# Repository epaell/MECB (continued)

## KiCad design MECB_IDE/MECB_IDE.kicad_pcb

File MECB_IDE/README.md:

# MECB IDE Board
An implementation of a parallel IDE board for the MECB system. The hardware is based on the PPIDE available for the RC2014 system (https://rc2014.co.uk/modules/ide-hard-drive-module/) and should be compatible with that and with RomWBW. The PLD is set to select the PPIDE device at ports $20-$23 (or $XX20-$XX23 on the MECB memory map if used with CPUs without a separate I/O map) - this is also the default port setting used by RomWBW. Here is the completed board with a compact FLASH to IDE adapter attached to the board:

I have confirmed that v1.0 of the board works using the 44-pin IDE connector. Note that Pin 20 of the 40 pin IDE header and the 44 pin IDE header should be removed as they act as a guide for devices/cables that plug directly into it:

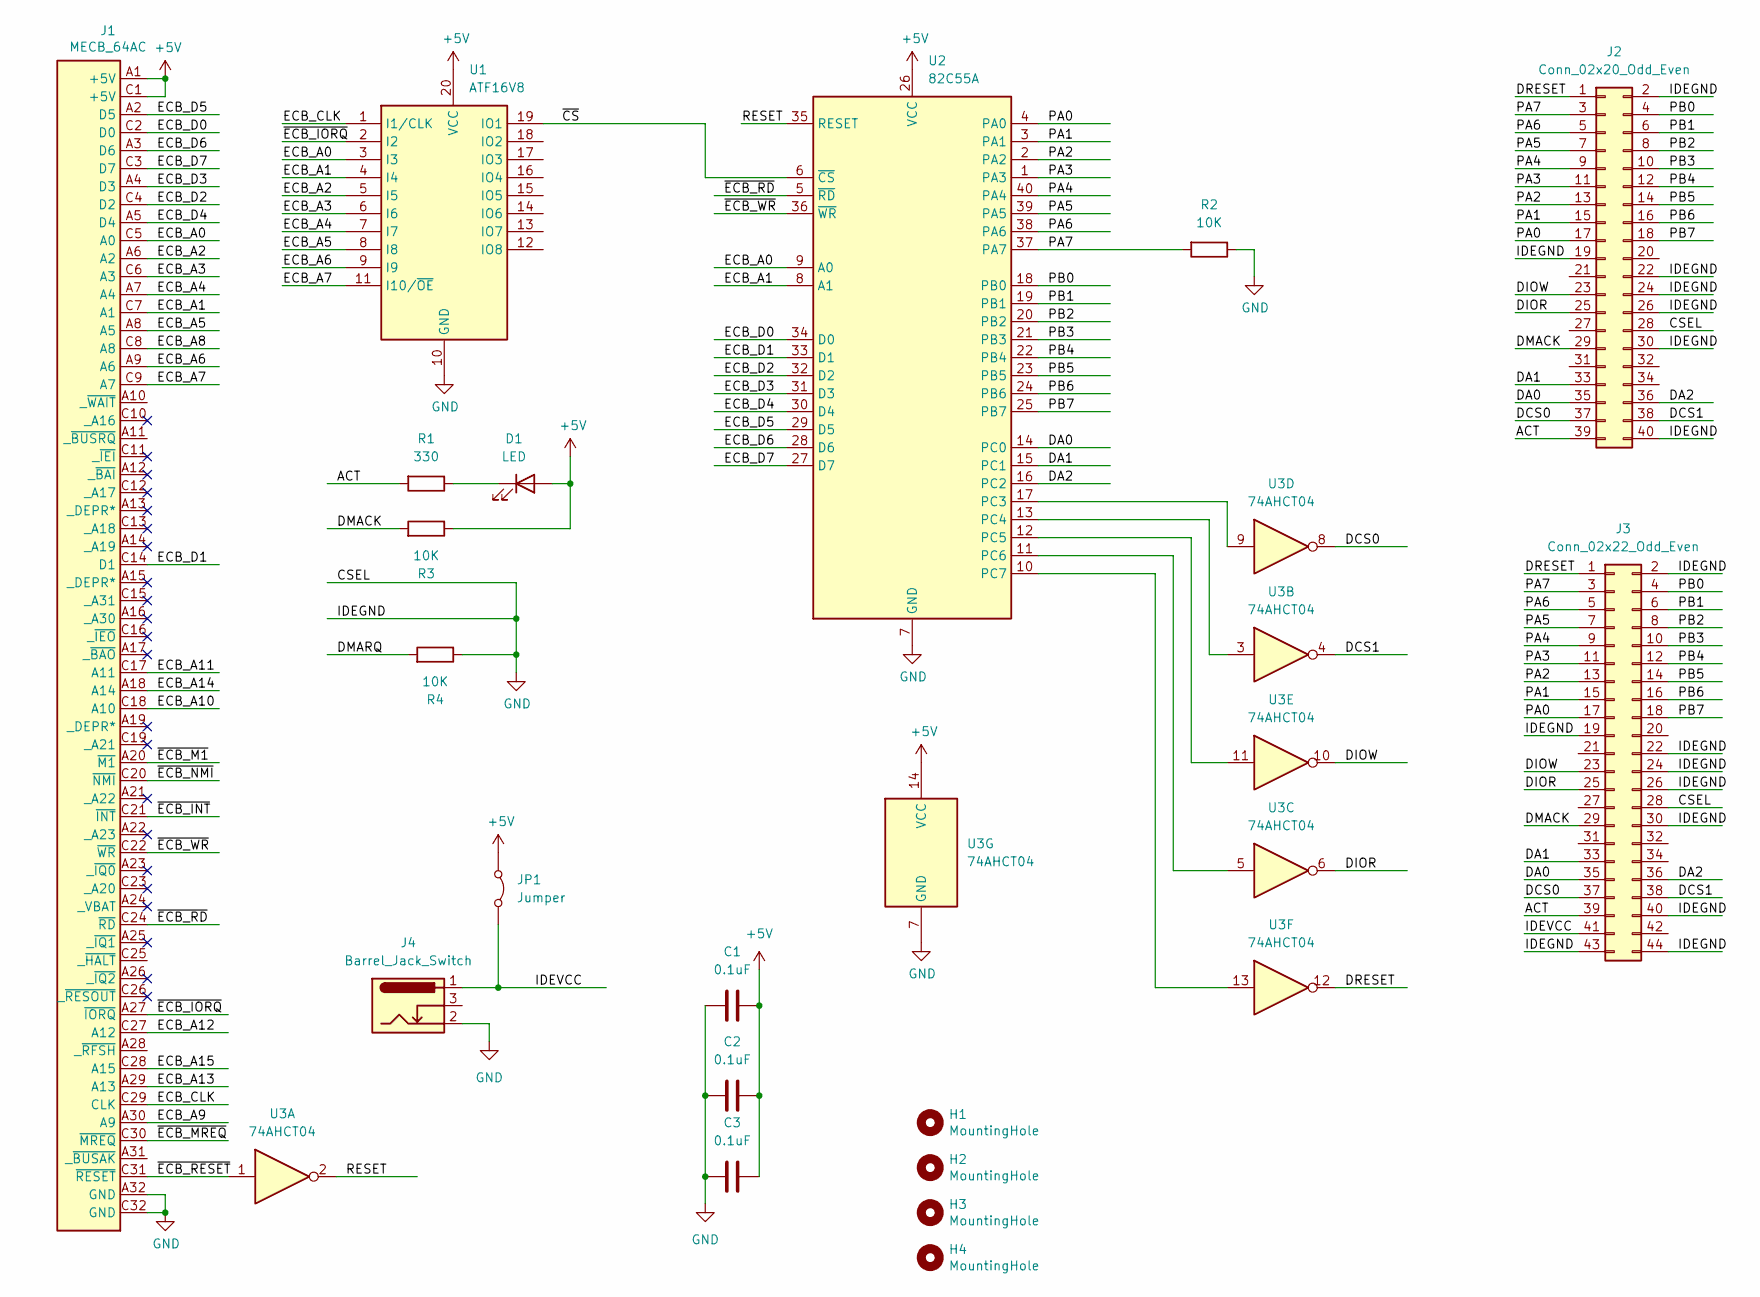
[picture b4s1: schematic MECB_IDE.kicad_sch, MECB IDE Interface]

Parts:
C1, C2, C3: 0.1uF; C_Disc_D5.0mm_W2.5mm_P5.00mm
D1: LED; LED_D3.0mm_Horizontal_O1.27mm_Z2.0mm
H1, H2, H3, H4: MountingHole; MountingHole_3.2mm_M3
J1: MECB_64AC; DIN41612_C_2x32_C64AC_Male_Horizontal_THT
J2: Conn_02x20_Odd_Even; IDC-Header_2x20_P2.54mm_Vertical
J3: Conn_02x22_Odd_Even; PinHeader_2x22_P2.00mm_Vertical
J4: Barrel_Jack_Switch; BarrelJack_Horizontal
JP1: Jumper; PinHeader_1x02_P2.54mm_Vertical
R1: 330; R_Axial_DIN0309_L9.0mm_D3.2mm_P12.70mm_Horizontal
R2, R3, R4: 10K; R_Axial_DIN0309_L9.0mm_D3.2mm_P12.70mm_Horizontal
U1: ATF16V8; DIP-20_W7.62mm_Socket_LongPads; Mouser Part Number 556-AF22V10C15PU
U2: 82C55A; DIP-40_W15.24mm_Socket_LongPads
U3: 74AHCT04; DIP-14_W7.62mm_Socket_LongPads

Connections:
+5V: C1.2, C2.2, C3.2, D1.2 (A), J1.A1 (+5V), J1.C1 (+5V), JP1.1 (A), R3.1, U1.20 (VCC), U2.26 (VCC), U3.14 (VCC)
/ACT: J2.39, J3.39, R1.2
/DA0: J2.35, J3.35, U2.14 (PC0)
/DA1: J2.33, J3.33, U2.15 (PC1)
/DA2: J2.36, J3.36, U2.16 (PC2)
/DCS0: J2.37, J3.37, U3.8
/DCS1: J2.38, J3.38, U3.4
/DIOR: J2.25, J3.25, U3.6
/DIOW: J2.23, J3.23, U3.10
/DMACK: J2.29, J3.29, R3.2
/DMARQ: R4.2
/DRESET: J2.1, J3.1, U3.12
/ECB_A0: J1.C5 (A0), U1.3 (I3), U2.9 (A0)
/ECB_A1: J1.C7 (A1), U1.4 (I4), U2.8 (A1)
/ECB_A2: J1.A6 (A2), U1.5 (I5)
/ECB_A3: J1.C6 (A3), U1.6 (I6)
/ECB_A4: J1.A7 (A4), U1.7 (I7)
/ECB_A5: J1.A8 (A5), U1.8 (I8)
/ECB_A6: J1.A9 (A6), U1.9 (I9)
/ECB_A7: J1.C9 (A7), U1.11 (I10/~OE)
/ECB_A8: J1.C8 (A8)
/ECB_A9: J1.A30 (A9)
/ECB_A10: J1.C18 (A10)
/ECB_A11: J1.C17 (A11)
/ECB_A12: J1.C27 (A12)
/ECB_A13: J1.A29 (A13)
/ECB_A14: J1.A18 (A14)
/ECB_A15: J1.C28 (A15)
/ECB_CLK: J1.C29 (CLK), U1.1 (I1/CLK)
/ECB_D0: J1.C2 (D0), U2.34 (D0)
/ECB_D1: J1.C14 (D1), U2.33 (D1)
/ECB_D2: J1.C4 (D2), U2.32 (D2)
/ECB_D3: J1.A4 (D3), U2.31 (D3)
/ECB_D4: J1.A5 (D4), U2.30 (D4)
/ECB_D5: J1.A2 (D5), U2.29 (D5)
/ECB_D6: J1.A3 (D6), U2.28 (D6)
/ECB_D7: J1.C3 (D7), U2.27 (D7)
/IDEVCC: J3.41, J4.1, JP1.2 (B)
/PA0: J2.17, J3.17, U2.4 (PA0)
/PA1: J2.15, J3.15, U2.3 (PA1)
/PA2: J2.13, J3.13, U2.2 (PA2)
/PA3: J2.11, J3.11, U2.1 (PA3)
/PA4: J2.9, J3.9, U2.40 (PA4)
/PA5: J2.7, J3.7, U2.39 (PA5)
/PA6: J2.5, J3.5, U2.38 (PA6)
/PA7: J2.3, J3.3, R2.2, U2.37 (PA7)
/PB0: J2.4, J3.4, U2.18 (PB0)
/PB1: J2.6, J3.6, U2.19 (PB1)
/PB2: J2.8, J3.8, U2.20 (PB2)
/PB3: J2.10, J3.10, U2.21 (PB3)
/PB4: J2.12, J3.12, U2.22 (PB4)
/PB5: J2.14, J3.14, U2.23 (PB5)
/PB6: J2.16, J3.16, U2.24 (PB6)
/PB7: J2.18, J3.18, U2.25 (PB7)
/RESET: U2.35 (RESET), U3.2
/~CS: U1.19 (IO1), U2.6 (~CS)
/~ECB_INT: J1.C21 (~INT)
/~ECB_IORQ: J1.A27 (~IORQ), U1.2 (I2)
/~ECB_M1: J1.A20 (~M1)
/~ECB_MREQ: J1.C30 (~MREQ)
/~ECB_NMI: J1.C20 (~NMI)
/~ECB_RD: J1.C24 (~RD), U2.5 (~RD)
/~ECB_RESET: J1.C31 (~RESET), U3.1
/~ECB_WR: J1.C22 (~WR), U2.36 (~WR)
GND: C1.1, C2.1, C3.1, J1.A32 (GND), J1.C32 (GND), J2.2, J2.19, J2.22, J2.24, J2.26, J2.28, J2.30, J2.40, J3.2, J3.19, J3.22, J3.24, J3.26, J3.28, J3.30, J3.40, J3.43, J3.44, J4.2, R2.1, R4.1, U1.10 (GND), U2.7 (GND), U3.7 (GND)
unnamed: D1.1 (K), R1.1
unnamed: U2.17 (PC3), U3.9
unnamed: U2.13 (PC4), U3.3
unnamed: U2.12 (PC5), U3.11
unnamed: U2.11 (PC6), U3.5
unnamed: U2.10 (PC7), U3.13

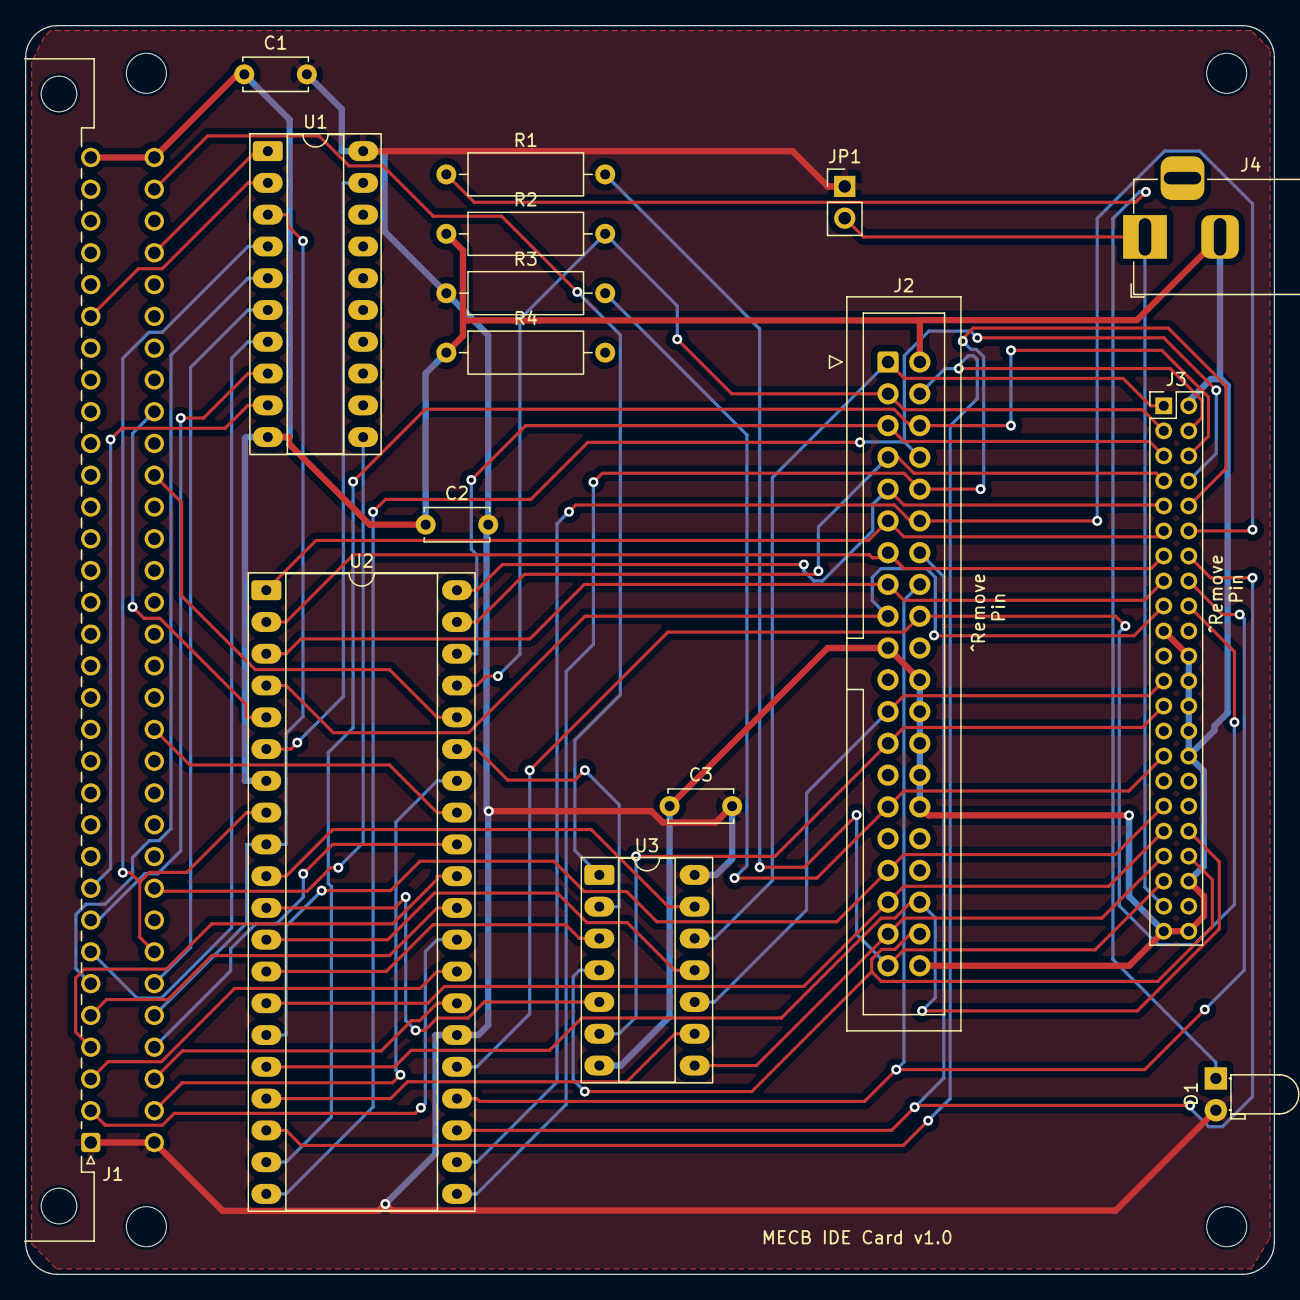
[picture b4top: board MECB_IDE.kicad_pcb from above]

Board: 2 copper layers, 99.8 x 99.8 mm, 20 parts (0 on the bottom side), 58 nets.

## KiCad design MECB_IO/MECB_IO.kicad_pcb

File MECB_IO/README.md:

# MECB_IO
An implementation of a basic I/O board for the MECB system. The hardware is based on a I/O and front panel design available
for the RC2014 system (https://rc2014.co.uk/backplanes/front-panel-kit/) and should be compatible with the Front Panel available for that. If using an external front panel do not install the on-board switches and LEDs.

The board also adds a Real-time clock and 31 bytes of non-volatile memory, again based on an RC2014 design (https://github.com/electrified/rc2014-ds1302-rtc/tree/main).

I have confirmed that the V1.0 version of the FP I/O board and RTC appear to be fully operational with MECB and RomWBW (though I haven't actually tested the front panel via an external cable). Note that the PLD places the RTC at $C0 (or $XXC0 for memory mapped CPUs) - this is the default location for RomWBW. The front panel I/O, however, is at $C1 (or $XXC1 for memory mapped CPUs) as opposed to the standard port of $00 (which conflicts with the MECB I/O board).

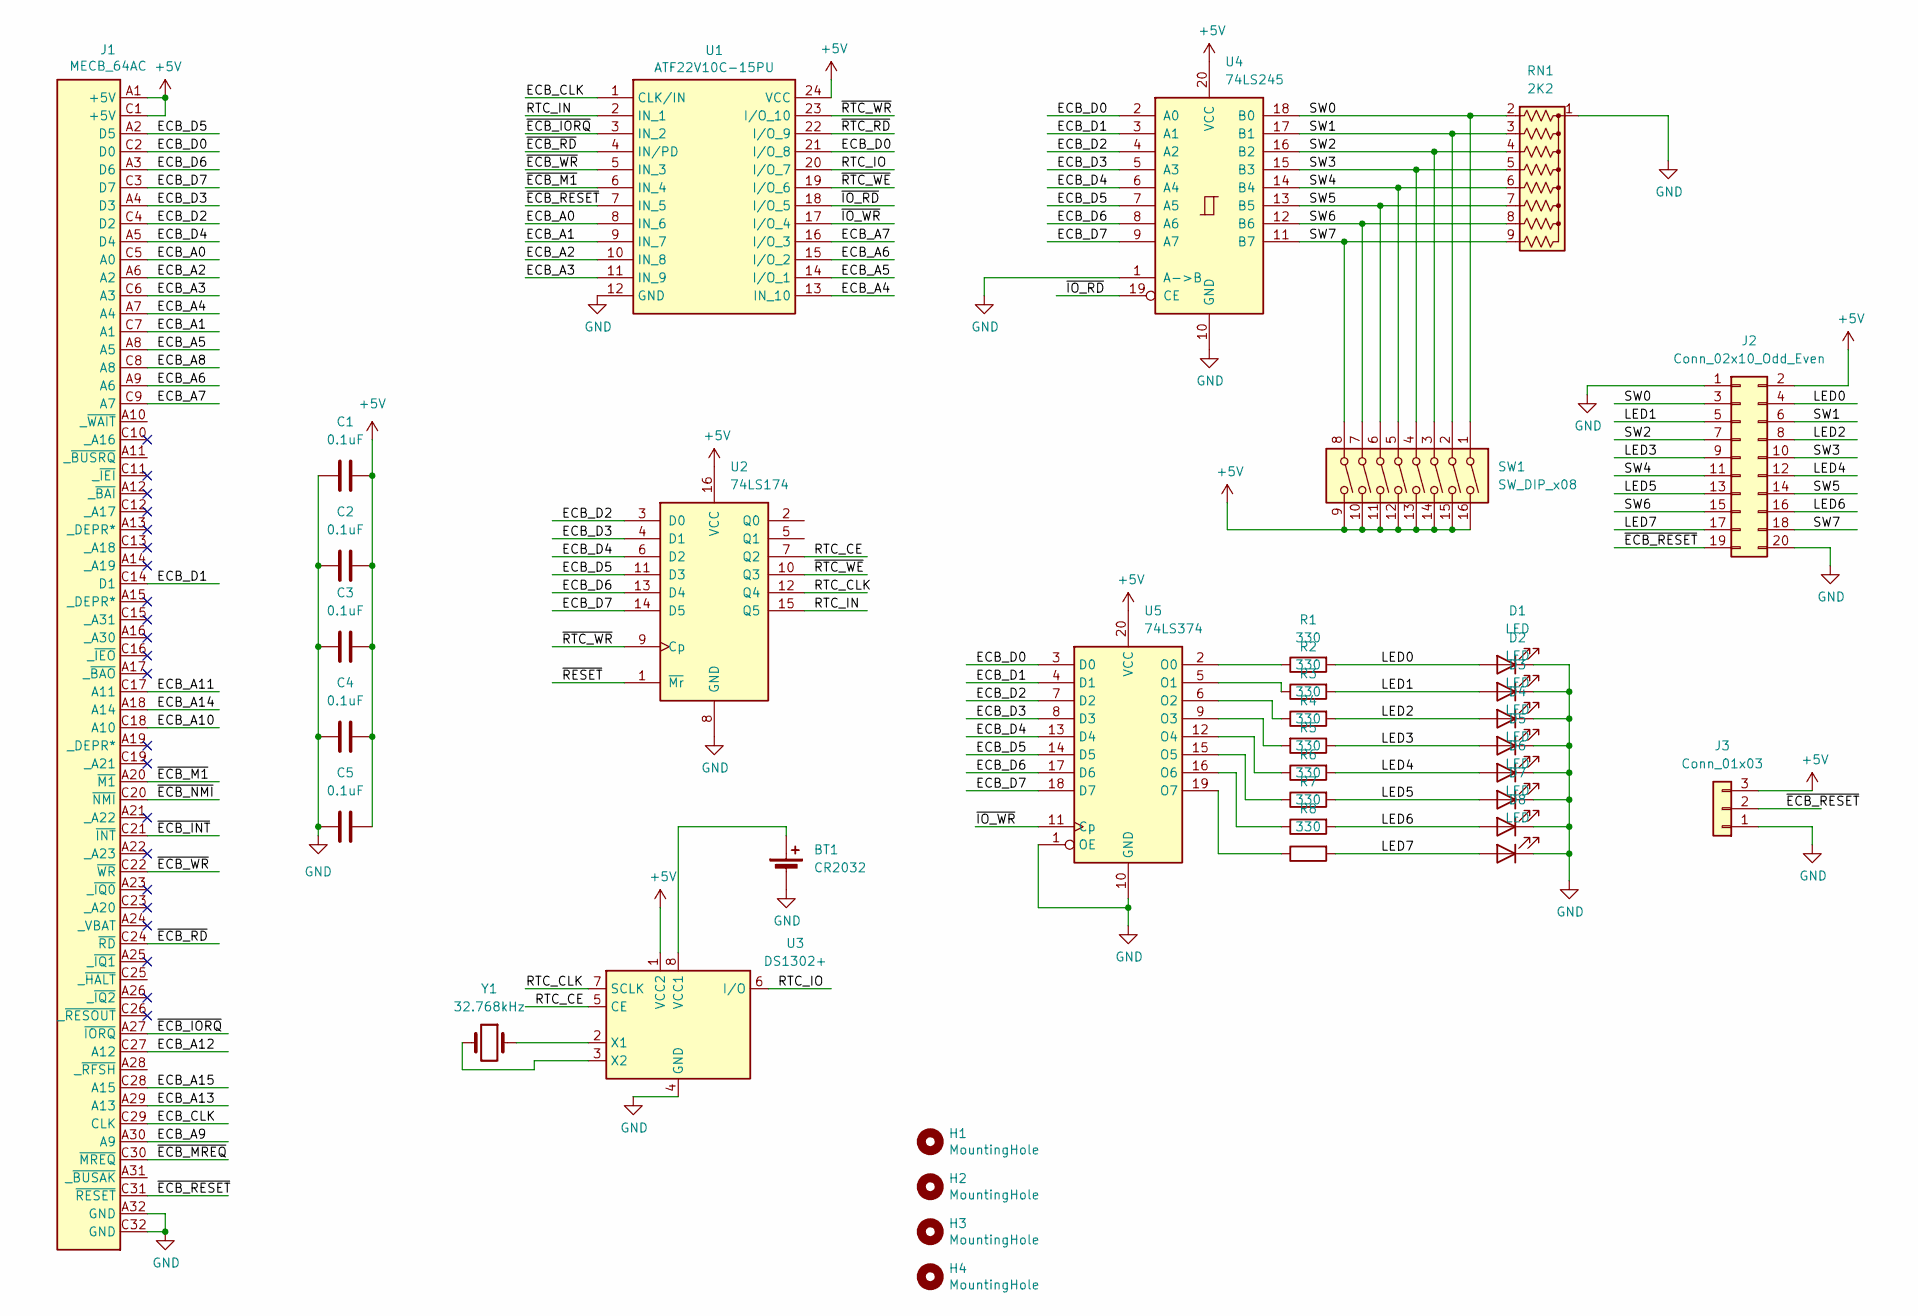
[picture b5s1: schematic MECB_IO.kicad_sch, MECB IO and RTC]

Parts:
BT1: CR2032; BatteryHolder_MYOUNG_BS-07-A1BJ001_CR2032
C1, C2, C3, C4, C5: 0.1uF; C_Disc_D5.0mm_W2.5mm_P5.00mm
D1, D2, D3, D4, D5, D6, D7, D8: LED; LED_D3.0mm_Horizontal_O1.27mm_Z2.0mm
H1, H2, H3, H4: MountingHole; MountingHole_3.2mm_M3
J1: MECB_64AC; DIN41612_C_2x32_C64AC_Male_Horizontal_THT
J2: Conn_02x10_Odd_Even; IDC-Header_2x10_P2.54mm_Vertical
J3: Conn_01x03; PinHeader_1x03_P2.54mm_Vertical
R1, R2, R3, R4, R5, R6, R7, R8: 330; R_Axial_DIN0309_L9.0mm_D3.2mm_P12.70mm_Horizontal
RN1: 2K2; R_Array_SIP9
SW1: SW_DIP_x08; DIP-16_W7.62mm_Socket_LongPads
U1: ATF22V10C-15PU; DIP-24_W7.62mm_Socket_LongPads_ZIF_Friendly; Mouser Part Number 556-AF22V10C15PU
U2: 74LS174; DIP-16_W7.62mm_Socket_LongPads
U3: DS1302+; DIP-8_W7.62mm_Socket_LongPads
U4: 74LS245; DIP-20_W7.62mm_Socket_LongPads
U5: 74LS374; DIP-20_W7.62mm_Socket_LongPads
Y1: 32.768kHz; Crystal_AT310_D3.0mm_L10.0mm_Horizontal

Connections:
+5V: C1.2, C2.2, C3.2, C4.2, C5.2, J1.A1 (+5V), J1.C1 (+5V), J2.2, J3.3, SW1.9, SW1.10, SW1.11, SW1.12, SW1.13, SW1.14, SW1.15, SW1.16, U1.24 (VCC), U2.16 (VCC), U3.1 (VCC2), U4.20 (VCC), U5.20 (VCC)
/ECB_A0: J1.C5 (A0), U1.8 (IN_6)
/ECB_A1: J1.C7 (A1), U1.9 (IN_7)
/ECB_A2: J1.A6 (A2), U1.10 (IN_8)
/ECB_A3: J1.C6 (A3), U1.11 (IN_9)
/ECB_A4: J1.A7 (A4), U1.13 (IN_10)
/ECB_A5: J1.A8 (A5), U1.14 (I/O_1)
/ECB_A6: J1.A9 (A6), U1.15 (I/O_2)
/ECB_A7: J1.C9 (A7), U1.16 (I/O_3)
/ECB_A8: J1.C8 (A8)
/ECB_A9: J1.A30 (A9)
/ECB_A10: J1.C18 (A10)
/ECB_A11: J1.C17 (A11)
/ECB_A12: J1.C27 (A12)
/ECB_A13: J1.A29 (A13)
/ECB_A14: J1.A18 (A14)
/ECB_A15: J1.C28 (A15)
/ECB_CLK: J1.C29 (CLK), U1.1 (CLK/IN)
/ECB_D0: J1.C2 (D0), U1.21 (I/O_8), U4.2 (A0), U5.3 (D0)
/ECB_D1: J1.C14 (D1), U4.3 (A1), U5.4 (D1)
/ECB_D2: J1.C4 (D2), U2.3 (D0), U4.4 (A2), U5.7 (D2)
/ECB_D3: J1.A4 (D3), U2.4 (D1), U4.5 (A3), U5.8 (D3)
/ECB_D4: J1.A5 (D4), U2.6 (D2), U4.6 (A4), U5.13 (D4)
/ECB_D5: J1.A2 (D5), U2.11 (D3), U4.7 (A5), U5.14 (D5)
/ECB_D6: J1.A3 (D6), U2.13 (D4), U4.8 (A6), U5.17 (D6)
/ECB_D7: J1.C3 (D7), U2.14 (D5), U4.9 (A7), U5.18 (D7)
/LED0: D1.2 (A), J2.4, R1.2
/LED1: D2.2 (A), J2.5, R2.2
/LED2: D3.2 (A), J2.8, R3.2
/LED3: D4.2 (A), J2.9, R4.1
/LED4: D5.2 (A), J2.12, R5.2
/LED5: D6.2 (A), J2.13, R6.2
/LED6: D7.2 (A), J2.16, R7.2
/LED7: D8.2 (A), J2.17, R8.2
/RTC_CE: U2.7 (Q2), U3.5 (CE)
/RTC_CLK: U2.12 (Q4), U3.7 (SCLK)
/RTC_IN: U1.2 (IN_1), U2.15 (Q5)
/RTC_IO: U1.20 (I/O_7), U3.6 (I/O)
/SW0: J2.3, RN1.2 (R1), SW1.1, U4.18 (B0)
/SW1: J2.6, RN1.3 (R2), SW1.2, U4.17 (B1)
/SW2: J2.7, RN1.4 (R3), SW1.3, U4.16 (B2)
/SW3: J2.10, RN1.5 (R4), SW1.4, U4.15 (B3)
/SW4: J2.11, RN1.6 (R5), SW1.5, U4.14 (B4)
/SW5: J2.14, RN1.7 (R6), SW1.6, U4.13 (B5)
/SW6: J2.15, RN1.8 (R7), SW1.7, U4.12 (B6)
/SW7: J2.18, RN1.9 (R8), SW1.8, U4.11 (B7)
/~ECB_INT: J1.C21 (~INT)
/~ECB_IORQ: J1.A27 (~IORQ), U1.3 (IN_2)
/~ECB_M1: J1.A20 (~M1), U1.6 (IN_4)
/~ECB_MREQ: J1.C30 (~MREQ)
/~ECB_NMI: J1.C20 (~NMI)
/~ECB_RD: J1.C24 (~RD), U1.4 (IN/PD)
/~ECB_RESET: J1.C31 (~RESET), J2.19, J3.2, U1.7 (IN_5)
/~ECB_WR: J1.C22 (~WR), U1.5 (IN_3)
/~IO_RD: U1.18 (I/O_5), U4.19 (CE)
/~IO_WR: U1.17 (I/O_4), U5.11 (Cp)
/~RESET: U2.1 (~Mr)
/~RTC_RD: U1.22 (I/O_9)
/~RTC_WE: U1.19 (I/O_6), U2.10 (Q3)
/~RTC_WR: U1.23 (I/O_10), U2.9 (Cp)
GND: BT1.2 (-), C1.1, C2.1, C3.1, C4.1, C5.1, D1.1 (K), D2.1 (K), D3.1 (K), D4.1 (K), D5.1 (K), D6.1 (K), D7.1 (K), D8.1 (K), J1.A32 (GND), J1.C32 (GND), J2.1, J2.20, J3.1, RN1.1 (common), U1.12 (GND), U2.8 (GND), U3.4 (GND), U4.1 (A->B), U4.10 (GND), U5.1 (OE), U5.10 (GND)
unnamed: BT1.1 (+), U3.8 (VCC1)
unnamed: U3.2 (X1), Y1.1
unnamed: U3.3 (X2), Y1.2
unnamed: R1.1, U5.2 (O0)
unnamed: R2.1, U5.5 (O1)
unnamed: R3.1, U5.6 (O2)
unnamed: R4.2, U5.9 (O3)
unnamed: R5.1, U5.12 (O4)
unnamed: R6.1, U5.15 (O5)
unnamed: R7.1, U5.16 (O6)
unnamed: R8.1, U5.19 (O7)

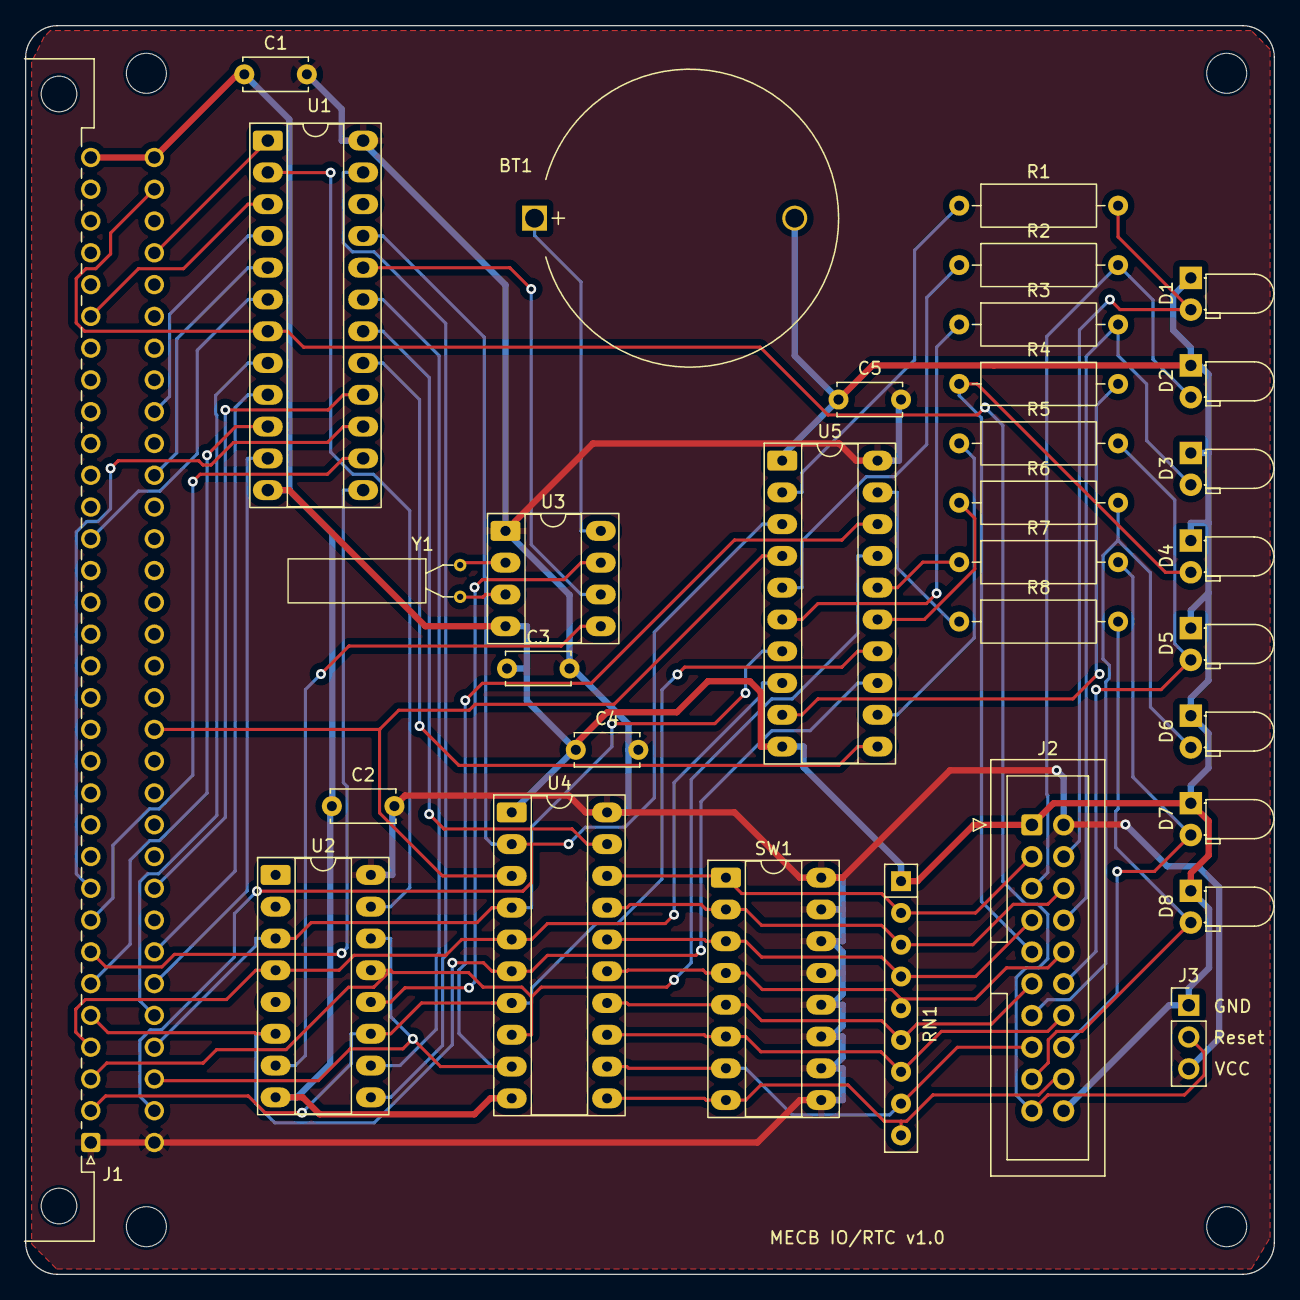
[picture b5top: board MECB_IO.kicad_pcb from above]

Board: 2 copper layers, 99.8 x 99.8 mm, 37 parts (0 on the bottom side), 59 nets.

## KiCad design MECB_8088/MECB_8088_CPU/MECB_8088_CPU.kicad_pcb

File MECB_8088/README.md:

# MECB_8088
Simple implementation of an Intel 8088 for the Digicool MECB system.

#GAL
Contains PLD definition files for the onboard PLD

#SW
Contains monitor and test programs.

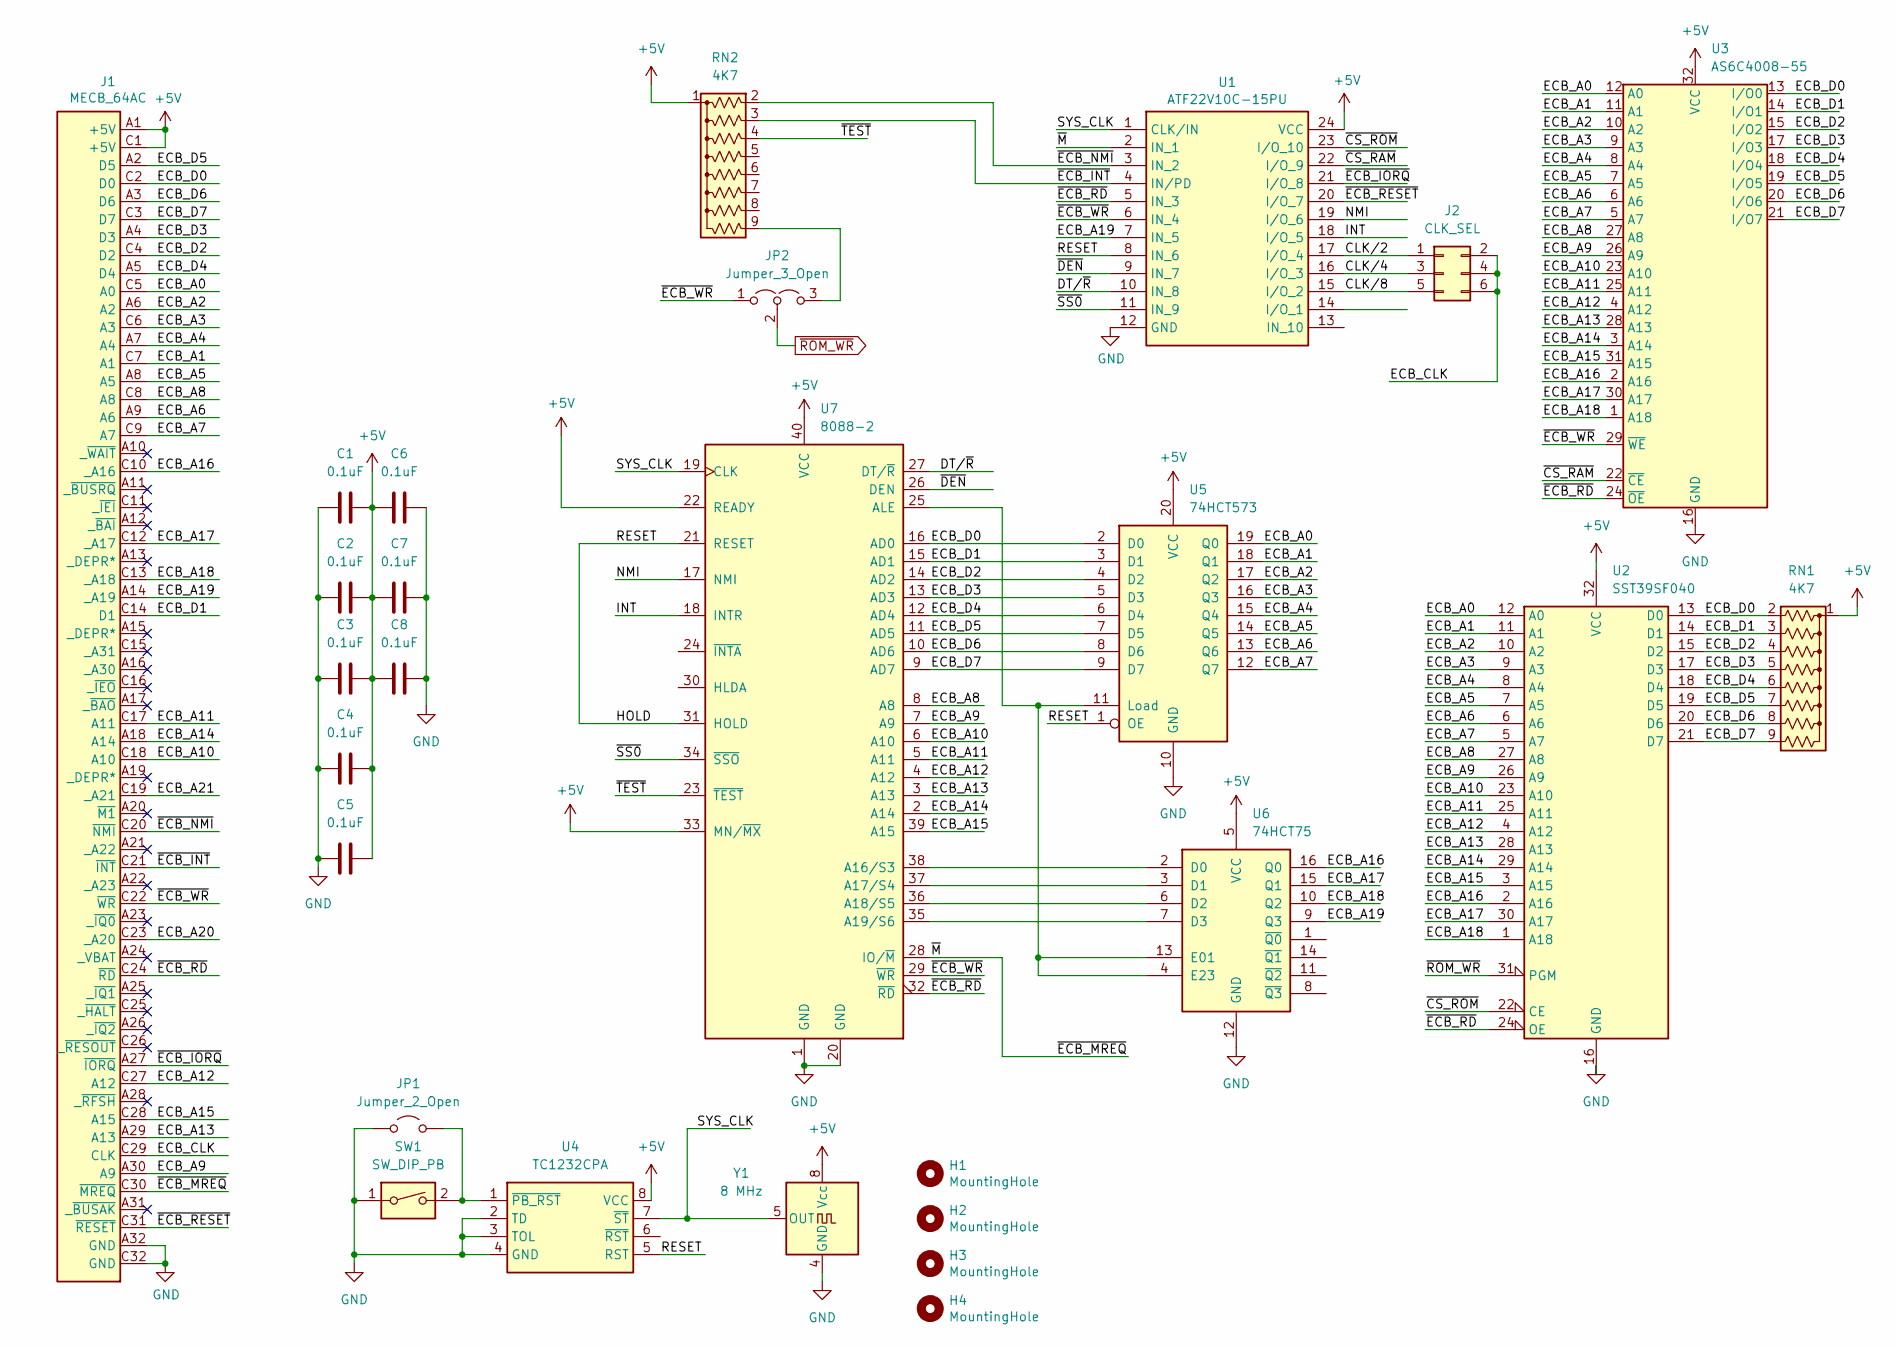
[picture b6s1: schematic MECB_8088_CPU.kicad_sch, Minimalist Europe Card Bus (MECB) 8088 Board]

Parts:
C1, C2, C3, C4, C5, C6, C7, C8: 0.1uF; C_Disc_D5.0mm_W2.5mm_P5.00mm
H1, H2, H3, H4: MountingHole; MountingHole_3.2mm_M3
J1: MECB_64AC; DIN41612_C_2x32_C64AC_Male_Horizontal_THT
J2: CLK_SEL; IDC-Header_2x03_P2.54mm_Vertical
JP1: Jumper_2_Open; PinHeader_1x02_P2.54mm_Vertical
JP2: Jumper_3_Open; PinHeader_1x03_P2.54mm_Vertical
RN1, RN2: 4K7; R_Array_SIP9
SW1: SW_DIP_PB; SW_Tactile_Straight_KSA0Axx1LFTR
U1: ATF22V10C-15PU; DIP-24_W7.62mm_Socket_LongPads_ZIF_Friendly; Mouser Part Number 556-AF22V10C15PU
U2: SST39SF040; DIP-32_W15.24mm_Socket_LongPads
U3: AS6C4008-55; DIP-32_W15.24mm_Socket_LongPads
U4: TC1232CPA; DIP-8_W7.62mm_Socket_LongPads
U5: 74HCT573; DIP-20_W7.62mm_Socket_LongPads
U6: 74HCT75; DIP-16_W7.62mm_Socket_LongPads
U7: 8088-2; DIP-40_W15.24mm_Socket_LongPads
Y1: 8 MHz; DIP-4-8_W7.62mm_Socket_LongPads

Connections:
+5V: C1.2, C2.2, C3.2, C4.2, C5.2, C6.1, C7.1, C8.1, J1.A1 (+5V), J1.C1 (+5V), RN1.1 (common), RN2.1 (common), U1.24 (VCC), U2.32 (VCC), U3.32 (VCC), U4.8 (VCC), U5.20 (VCC), U6.5 (VCC), U7.22 (READY), U7.33 (MN/~MX), U7.40 (VCC), Y1.8 (Vcc)
/CLK/2: J2.1, U1.17 (I/O_4)
/CLK/4: J2.3, U1.16 (I/O_3)
/CLK/8: J2.5, U1.15 (I/O_2)
/DT/~R: U1.10 (IN_8), U7.27 (DT/~R)
/ECB_A0: J1.C5 (A0), U2.12 (A0), U3.12 (A0), U5.19 (Q0)
/ECB_A1: J1.C7 (A1), U2.11 (A1), U3.11 (A1), U5.18 (Q1)
/ECB_A2: J1.A6 (A2), U2.10 (A2), U3.10 (A2), U5.17 (Q2)
/ECB_A3: J1.C6 (A3), U2.9 (A3), U3.9 (A3), U5.16 (Q3)
/ECB_A4: J1.A7 (A4), U2.8 (A4), U3.8 (A4), U5.15 (Q4)
/ECB_A5: J1.A8 (A5), U2.7 (A5), U3.7 (A5), U5.14 (Q5)
/ECB_A6: J1.A9 (A6), U2.6 (A6), U3.6 (A6), U5.13 (Q6)
/ECB_A7: J1.C9 (A7), U2.5 (A7), U3.5 (A7), U5.12 (Q7)
/ECB_A8: J1.C8 (A8), U2.27 (A8), U3.27 (A8), U7.8 (A8)
/ECB_A9: J1.A30 (A9), U2.26 (A9), U3.26 (A9), U7.7 (A9)
/ECB_A10: J1.C18 (A10), U2.23 (A10), U3.23 (A10), U7.6 (A10)
/ECB_A11: J1.C17 (A11), U2.25 (A11), U3.25 (A11), U7.5 (A11)
/ECB_A12: J1.C27 (A12), U2.4 (A12), U3.4 (A12), U7.4 (A12)
/ECB_A13: J1.A29 (A13), U2.28 (A13), U3.28 (A13), U7.3 (A13)
/ECB_A14: J1.A18 (A14), U2.29 (A14), U3.3 (A14), U7.2 (A14)
/ECB_A15: J1.C28 (A15), U2.3 (A15), U3.31 (A15), U7.39 (A15)
/ECB_A16: J1.C10 (_A16), U2.2 (A16), U3.2 (A16), U6.16 (Q0)
/ECB_A17: J1.C12 (_A17), U2.30 (A17), U3.30 (A17), U6.15 (Q1)
/ECB_A18: J1.C13 (_A18), U2.1 (A18), U3.1 (A18), U6.10 (Q2)
/ECB_A19: J1.A14 (_A19), U1.7 (IN_5), U6.9 (Q3)
/ECB_A20: J1.C23 (_A20)
/ECB_A21: J1.C19 (_A21)
/ECB_CLK: J1.C29 (CLK), J2.2, J2.4, J2.6
/ECB_D0: J1.C2 (D0), RN1.2 (R1), U2.13 (D0), U3.13 (I/O0), U5.2 (D0), U7.16 (AD0)
/ECB_D1: J1.C14 (D1), RN1.3 (R2), U2.14 (D1), U3.14 (I/O1), U5.3 (D1), U7.15 (AD1)
/ECB_D2: J1.C4 (D2), RN1.4 (R3), U2.15 (D2), U3.15 (I/O2), U5.4 (D2), U7.14 (AD2)
/ECB_D3: J1.A4 (D3), RN1.5 (R4), U2.17 (D3), U3.17 (I/O3), U5.5 (D3), U7.13 (AD3)
/ECB_D4: J1.A5 (D4), RN1.6 (R5), U2.18 (D4), U3.18 (I/O4), U5.6 (D4), U7.12 (AD4)
/ECB_D5: J1.A2 (D5), RN1.7 (R6), U2.19 (D5), U3.19 (I/O5), U5.7 (D5), U7.11 (AD5)
/ECB_D6: J1.A3 (D6), RN1.8 (R7), U2.20 (D6), U3.20 (I/O6), U5.8 (D6), U7.10 (AD6)
/ECB_D7: J1.C3 (D7), RN1.9 (R8), U2.21 (D7), U3.21 (I/O7), U5.9 (D7), U7.9 (AD7)
/HOLD: U1.8 (IN_6), U4.5 (RST), U5.1 (OE), U7.21 (RESET), U7.31 (HOLD)
/INT: U1.18 (I/O_5), U7.18 (INTR)
/NMI: U1.19 (I/O_6), U7.17 (NMI)
/SYS_CLK: U1.1 (CLK/IN), U4.7 (~ST), U7.19 (CLK), Y1.5 (OUT)
/~CS_RAM: U1.22 (I/O_9), U3.22 (~CE)
/~CS_ROM: U1.23 (I/O_10), U2.22 (CE)
/~DEN: U1.9 (IN_7), U7.26 (DEN)
/~ECB_INT: J1.C21 (~INT), RN2.3 (R2), U1.4 (IN/PD)
/~ECB_IORQ: J1.A27 (~IORQ), U1.21 (I/O_8)
/~ECB_MREQ: J1.C30 (~MREQ), U1.2 (IN_1), U7.28 (IO/~M)
/~ECB_NMI: J1.C20 (~NMI), RN2.2 (R1), U1.3 (IN_2)
/~ECB_RD: J1.C24 (~RD), U1.5 (IN_3), U2.24 (OE), U3.24 (~OE), U7.32 (~RD)
/~ECB_RESET: J1.C31 (~RESET), U1.20 (I/O_7)
/~ECB_WR: J1.C22 (~WR), JP2.1 (A), U1.6 (IN_4), U3.29 (~WE), U7.29 (~WR)
/~SS0: U1.11 (IN_9), U7.34 (~SSO)
/~TEST: RN2.4 (R3), U7.23 (~TEST)
GND: C1.1, C2.1, C3.1, C4.1, C5.1, C6.2, C7.2, C8.2, J1.A32 (GND), J1.C32 (GND), JP1.1 (A), SW1.1, U1.12 (GND), U2.16 (GND), U3.16 (GND), U4.2 (TD), U4.3 (TOL), U4.4 (GND), U5.10 (GND), U6.12 (GND), U7.1 (GND), U7.20 (GND), Y1.4 (GND)
unnamed: JP1.2 (B), SW1.2, U4.1 (~PB_RST)
unnamed: JP2.3 (B), RN2.9 (R8)
unnamed: U5.11 (Load), U6.4 (E23), U6.13 (E01), U7.25 (ALE)
unnamed: U6.2 (D0), U7.38 (A16/S3)
unnamed: U6.3 (D1), U7.37 (A17/S4)
unnamed: U6.6 (D2), U7.36 (A18/S5)
unnamed: U6.7 (D3), U7.35 (A19/S6)
~ROM_WR: JP2.2 (C), U2.31 (PGM)

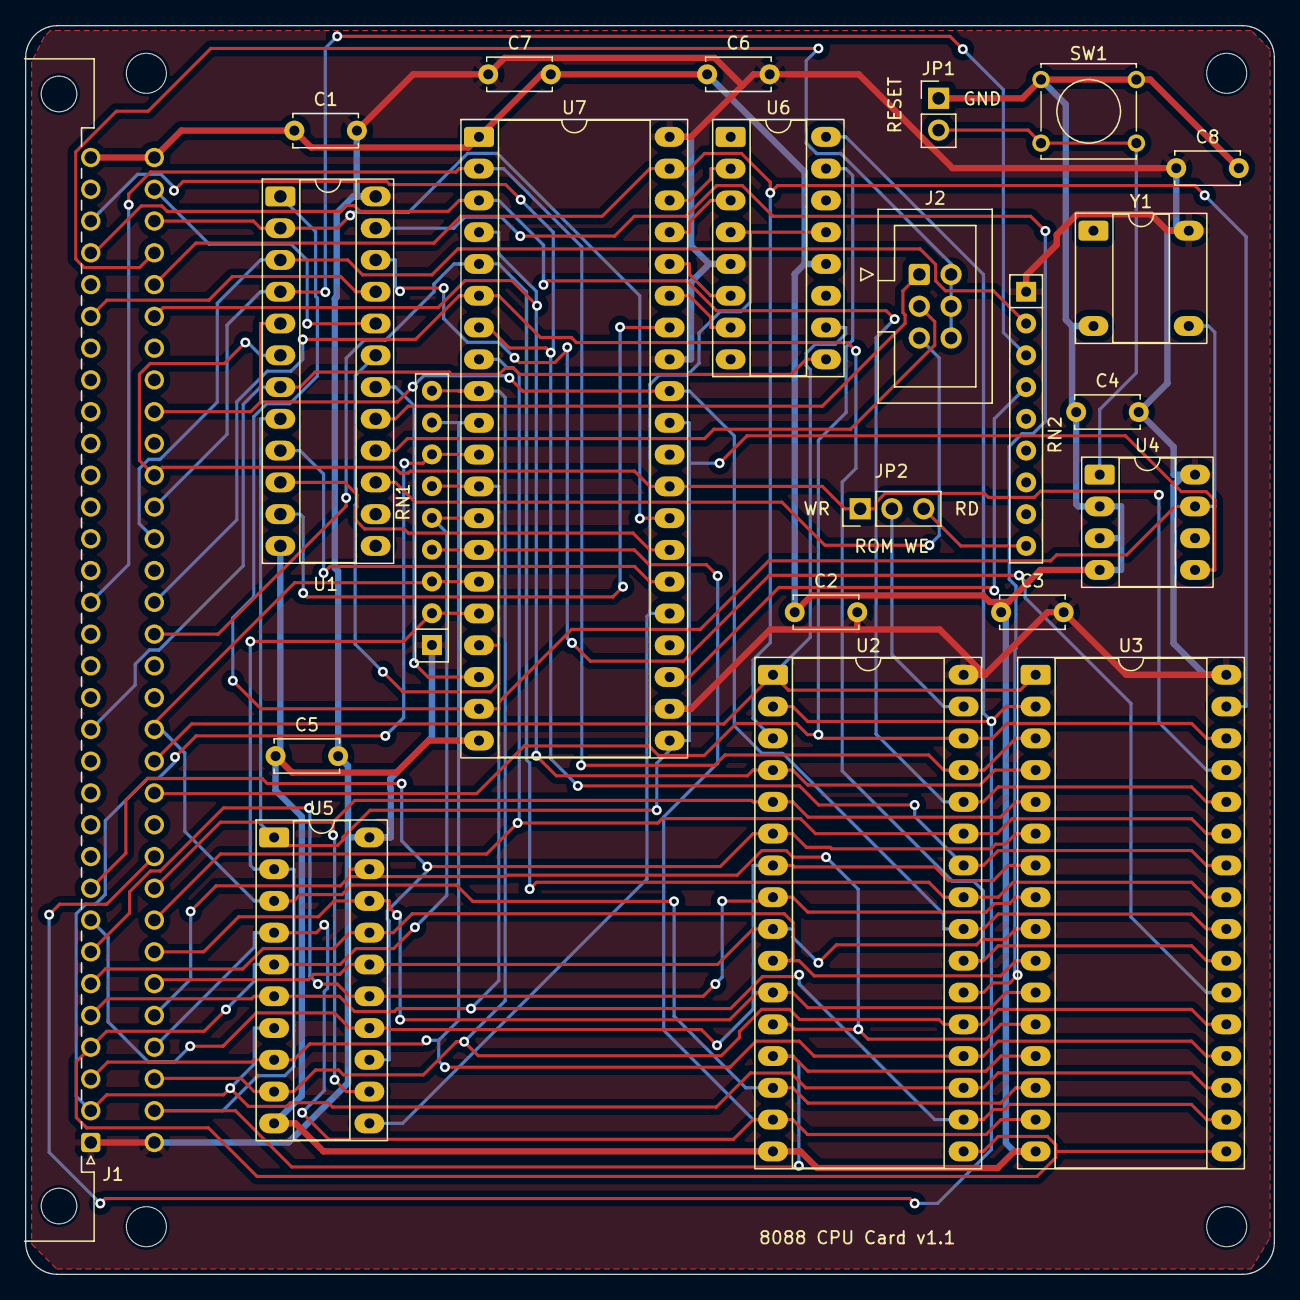
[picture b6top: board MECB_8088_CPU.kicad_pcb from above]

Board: 2 copper layers, 99.8 x 99.8 mm, 27 parts (0 on the bottom side), 59 nets.
